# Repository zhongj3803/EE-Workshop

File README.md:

# EE-Workshop
Repository for EE Workshop material

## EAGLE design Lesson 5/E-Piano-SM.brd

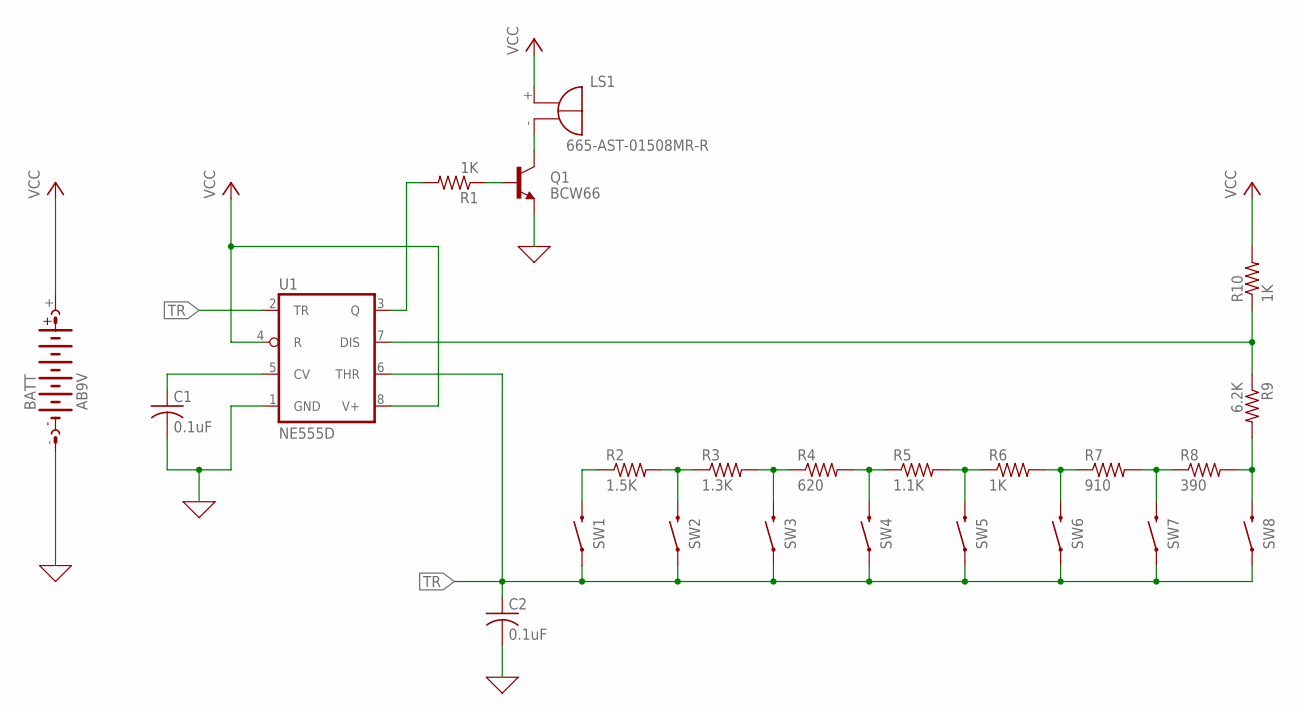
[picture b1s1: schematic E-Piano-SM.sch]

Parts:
BATT: AB9V
C1, C2: 0.1uF; C0805; MOUSER# 791-MT21B104K500CT
LS1: F/HMB; MOUSER# 665-AST-01508MR-R
Q1: BCW66; SOT23-BEC; MOUSER# 726-BCW66KHE6327HTSA
R1, R6, R10: 1K; R0805; MOUSER# 652-CR0805FX-1001ELF
R2: 1.5K; R0805; MOUSER# 652-CR0805FX-1501ELF
R3: 1.3K; R0805; MOUSER# 652-CR0805JW-132ELF
R4: 620; R0805; MOUSER# 652-CR0805JW-621ELF
R5: 1.1K; R0805; MOUSER# 652-CR0805FX-1101ELF
R7: 910; R0805; MOUSER# 652-CR0805FX-9100ELF
R8: 390; R0805; MOUSER# 652-CR0805JW-391ELF
R9: 6.2K; R0805; MOUSER# 652-CR0805FX-6201ELF
SW1, SW2, SW3, SW4, SW5, SW6, SW7, SW8: MOMENTARY-SWITCH-SPST-SMD-6.2MM-TALL; TACTILE_SWITCH_SMD_6.2MM_TALL; MOUSER# 653-B3F-1000
U1: NE555D; SO08; MOUSER# 595-TLC555CDR

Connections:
0: BATT.-, C1.2, C2.2, Q1.E, U1.1 (GND)
unnamed: R8.2, R9.2, SW8.B2 (2)
unnamed: R9.1, R10.1, U1.7 (DIS)
unnamed: R2.1, SW1.B2 (2)
unnamed: R7.2, R8.1, SW7.B2 (2)
unnamed: R6.2, R7.1, SW6.B2 (2)
unnamed: R5.2, R6.1, SW5.B2 (2)
unnamed: R4.2, R5.1, SW4.B2 (2)
unnamed: R3.2, R4.1, SW3.B2 (2)
unnamed: R2.2, R3.1, SW2.B2 (2)
unnamed: R1.2, U1.3 (Q)
unnamed: C1.1, U1.5 (CV)
unnamed: LS1.-, Q1.C
unnamed: Q1.B, R1.1
TR: C2.1, SW1.A2 (1), SW2.A2 (1), SW3.A2 (1), SW4.A2 (1), SW5.A2 (1), SW6.A2 (1), SW7.A2 (1), SW8.A2 (1), U1.2 (TR), U1.6 (THR)
VCC: BATT.+, LS1.+, R10.2, U1.4 (R), U1.8 (V+)

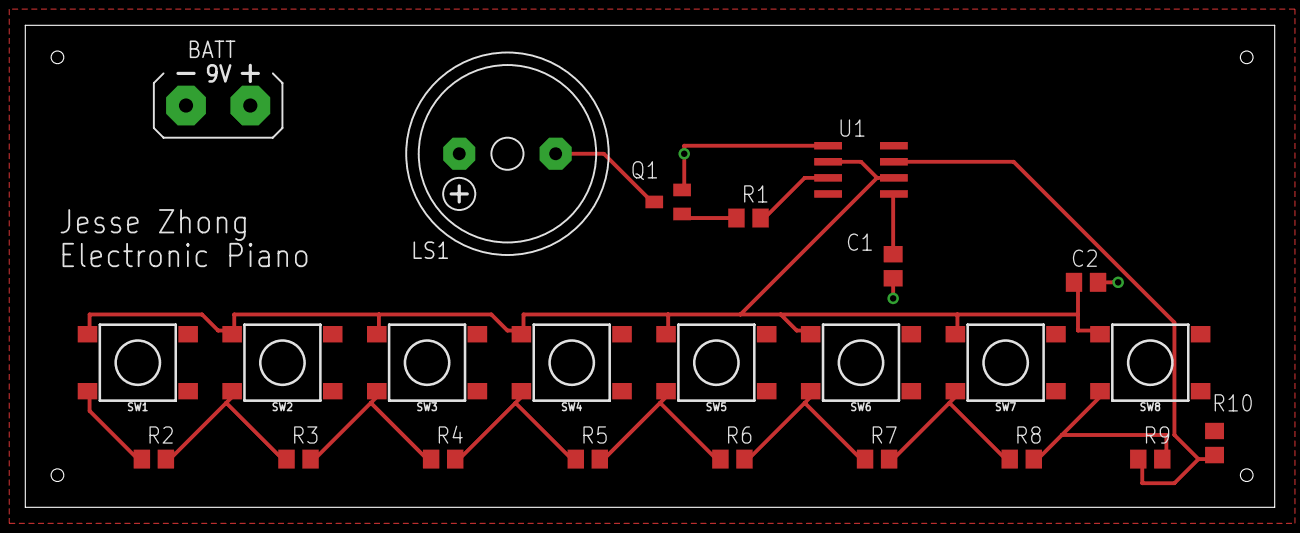
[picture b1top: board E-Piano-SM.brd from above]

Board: 2 copper layers, 98.7 x 38.1 mm, 24 parts (0 on the bottom side), 16 nets.

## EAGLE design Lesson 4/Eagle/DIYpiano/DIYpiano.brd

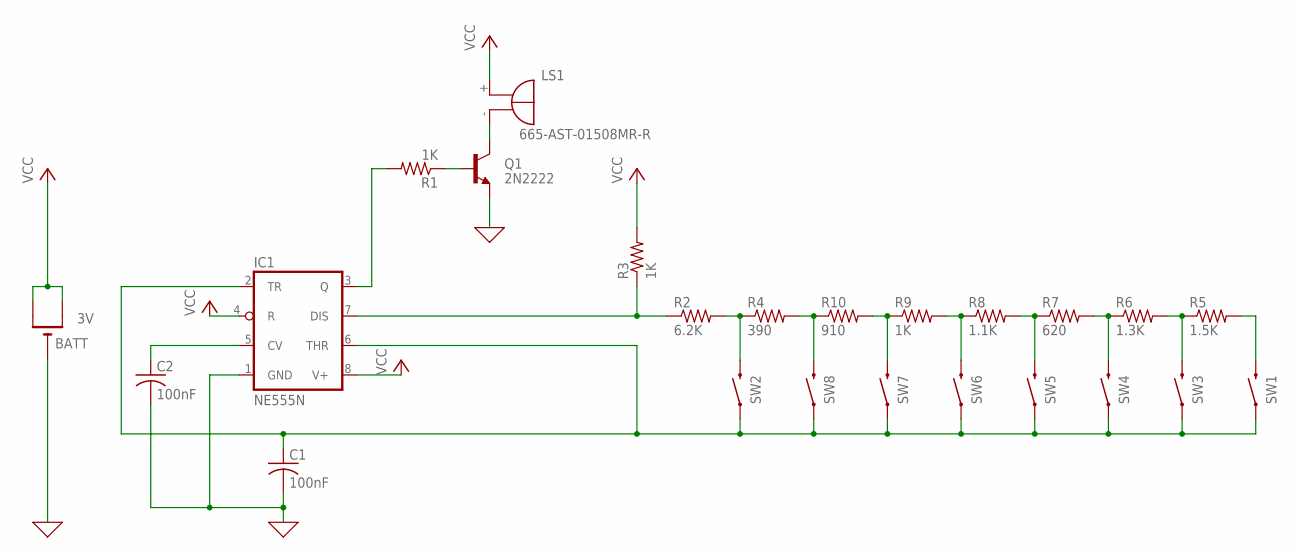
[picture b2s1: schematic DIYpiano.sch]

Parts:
BATT: 3V; CR1220-THM; MOUSER# 534-3001
C1, C2: 100nF; C025-025X050; MOUSER# 581-SR201C104KARTR1
IC1: NE555N; DIL08; MOUSER# 595-TLC555CP
LS1: F/HMB; MOUSER# 665-AST-01508MR-R
Q1: 2N2222; TO92-E1; MOUSER# 833-PN2222A-AP
R1, R3, R9: 1K; 0207/10; MOUSER# 660-MF1/4DCT26A1001F
R2: 6.2K; 0207/10; MOUSER# 603-MFR-25FRF52-6K2
R4: 390; 0207/10; MOUSER# 603-MFR-25FTE52-390R
R5: 1.5K; 0207/10; MOUSER# 603-MFR-25FBF52-1K5
R6: 1.3K; 0207/10; MOUSER# 603-MFR-25FBF52-1K3
R7: 620; 0207/10; MOUSER# 603-MFR-25FBF52-620R
R8: 1.1K; 0207/10; MOUSER# 603-MFR-25FBF52-1K1
R10: 910; 0207/10; MOUSER# 603-MFR-25FRF52-910R
SW1, SW2, SW3, SW4, SW5, SW6, SW7, SW8: MOMENTARY-SWITCH-SPST-PTH-6.0MM; TACTILE_SWITCH_PTH_6.0MM; MOUSER# 653-B3F-1000

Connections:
GND: BATT.-, C1.2, C2.2, IC1.1 (GND), Q1.3 (E)
unnamed: R2.2, R4.1, SW2.3 (2)
unnamed: IC1.7 (DIS), R2.1, R3.1
unnamed: C1.1, IC1.2 (TR), IC1.6 (THR), SW1.1, SW2.1, SW3.1, SW4.1, SW5.1, SW6.1, SW7.1, SW8.1
unnamed: R4.2, R10.1, SW8.3 (2)
unnamed: R9.1, R10.2, SW7.3 (2)
unnamed: R8.1, R9.2, SW6.3 (2)
unnamed: R7.1, R8.2, SW5.3 (2)
unnamed: R6.1, R7.2, SW4.3 (2)
unnamed: R5.1, R6.2, SW3.3 (2)
unnamed: R5.2, SW1.3 (2)
unnamed: IC1.3 (Q), R1.2
unnamed: C2.1, IC1.5 (CV)
unnamed: LS1.-, Q1.1 (C)
unnamed: Q1.2 (B), R1.1
VCC: BATT.+1 (+), BATT.+2 (+1), IC1.4 (R), IC1.8 (V+), LS1.+, R3.2

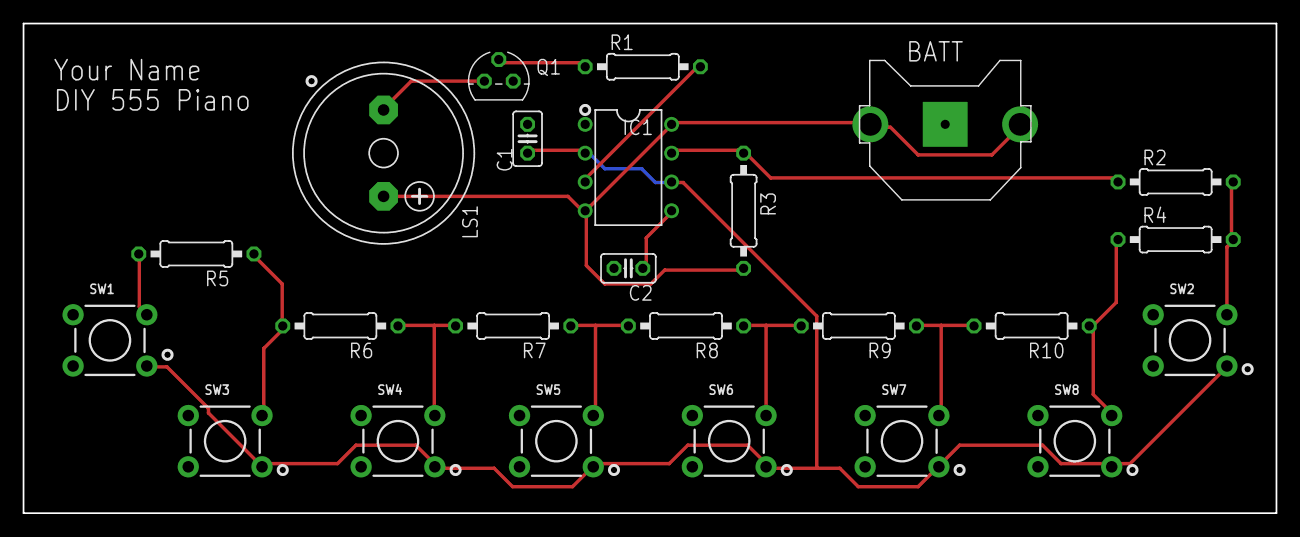
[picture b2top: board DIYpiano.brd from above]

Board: 2 copper layers, 110.5 x 43.2 mm, 24 parts (0 on the bottom side), 16 nets.

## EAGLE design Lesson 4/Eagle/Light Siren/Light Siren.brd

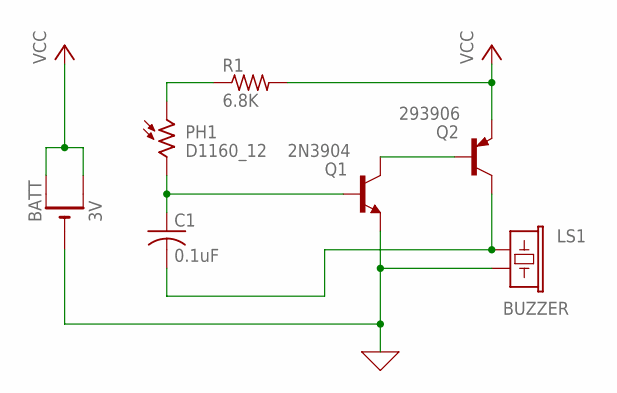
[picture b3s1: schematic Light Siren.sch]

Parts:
BATT: 3V; CR1220-THM
C1: 0.1uF; C025-025X050
LS1: BUZZER; BUZZER-12MM-NS
PH1: D1160_12; D11XX
Q1: 2N3904; TO92
Q2: 293906; TO92
R1: 6.8K; 0207/10

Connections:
0: BATT.-, LS1.- (2), Q1.1 (E)
unnamed: PH1.1, R1.1
unnamed: C1.2, LS1.+ (1), Q2.3 (C)
unnamed: Q1.3 (C), Q2.2 (B)
unnamed: C1.1, PH1.2, Q1.2 (B)
VCC: BATT.+1 (+), BATT.+2 (+1), Q2.1 (E), R1.2

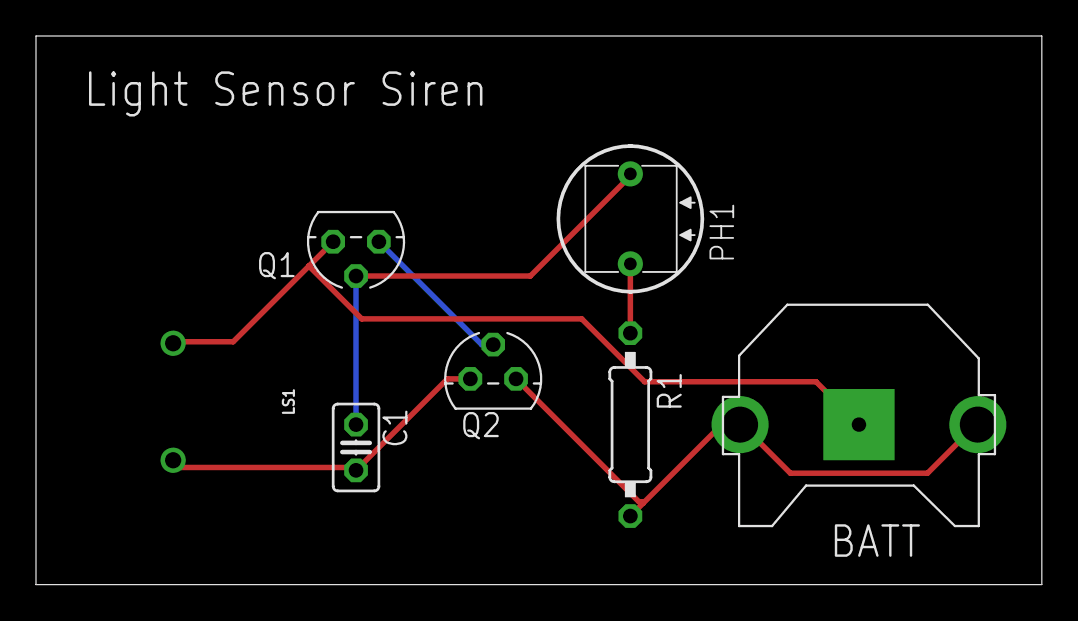
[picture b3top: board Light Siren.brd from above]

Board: 2 copper layers, 55.9 x 30.5 mm, 7 parts (0 on the bottom side), 6 nets.

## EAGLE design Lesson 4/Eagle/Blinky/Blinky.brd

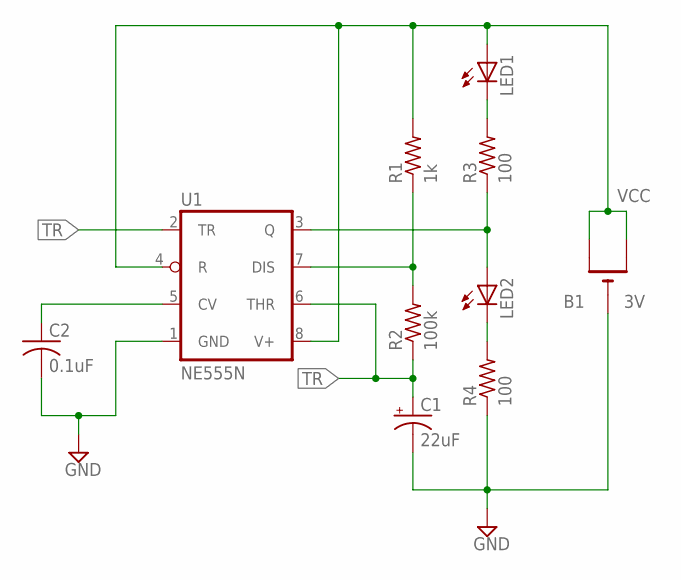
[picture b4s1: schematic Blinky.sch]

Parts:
B1: 3V; CR1220-THM
C1: 22uF; E1,8-4
C2: 0.1uF; C025-025X050
LED1, LED2: LED5MM
R1: 1k; 0309/12
R2: 100k; 0309/12
R3, R4: 100; 0309/12
U1: NE555N; DIL08

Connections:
GND: B1.-, C1.-, C2.2, R4.1, U1.1 (GND)
unnamed: C2.1, U1.5 (CV)
unnamed: R1.1, R2.2, U1.7 (DIS)
unnamed: LED2.A, R3.1, U1.3 (Q)
unnamed: LED2.K (C), R4.2
unnamed: LED1.K (C), R3.2
TR: C1.+, R2.1, U1.2 (TR), U1.6 (THR)
VCC: B1.+1 (+), B1.+2 (+1), LED1.A, R1.2, U1.4 (R), U1.8 (V+)

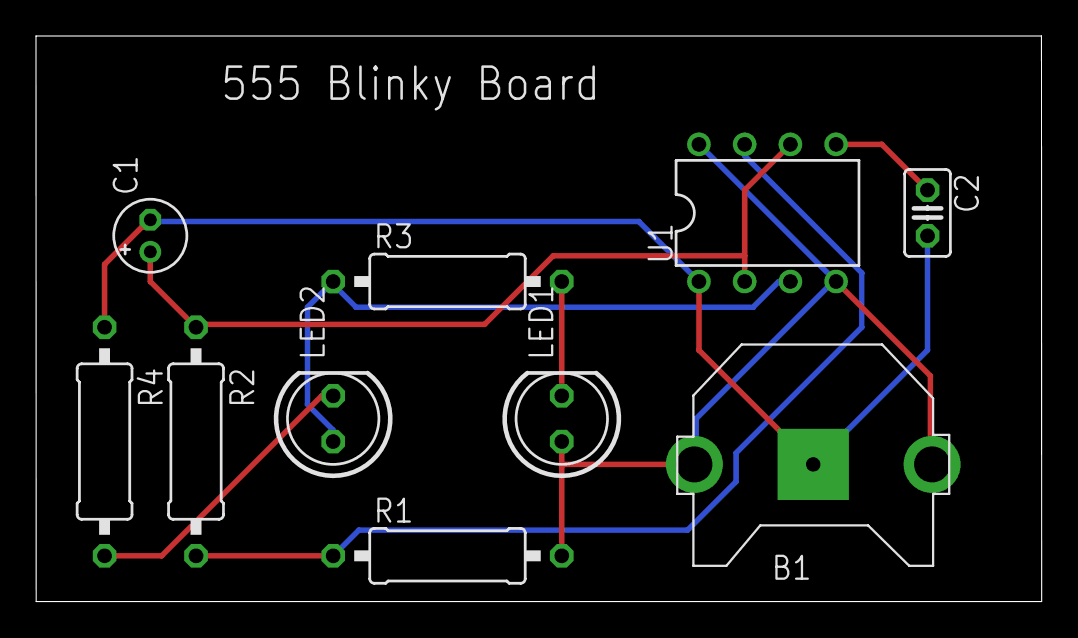
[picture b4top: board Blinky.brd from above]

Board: 2 copper layers, 55.9 x 31.4 mm, 10 parts (0 on the bottom side), 8 nets.

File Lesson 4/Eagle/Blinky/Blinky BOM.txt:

Partlist exported from C:/Users/Parents/Documents/League/GitHub/EE-Workshop/Lesson 4/Eagle/Blinky/Blinky.sch at 12/1/2018 8:56 AM

Part Value  Device          Package      Description                                    SPICEPREFIX
B1   3V     CR1220THM       CR1220-THM   CR1216/CR1220/CR1225 12mm 3V lithium coin cell J          
C1   22uF   CPOL-USE1.8-4   E1,8-4       POLARIZED CAPACITOR, American symbol           C          
C2   0.1uF  C-US025-025X050 C025-025X050 CAPACITOR, American symbol                     C          
LED1        LED5MM          LED5MM       LED                                                       
LED2        LED5MM          LED5MM       LED                                                       
R1   1k     R-US_0309/12    0309/12      RESISTOR, American symbol                      R          
R2   100k   R-US_0309/12    0309/12      RESISTOR, American symbol                      R          
R3   100    R-US_0309/12    0309/12      RESISTOR, American symbol                      R          
R4   100    R-US_0309/12    0309/12      RESISTOR, American symbol                      R          
U1   NE555N NE555N          DIL08        TIMER                                          X

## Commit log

2018-10-19 Initial upload of LTSpice schematics
2018-10-19 Updating the Circuits directory
    Many new schematics and accomponying spreadsheets have been added.
    Pendant was moved from LTSpice to the "Circuits" directory.
2018-11-09 Updates and upload of the Pentdant Design
2018-11-16 Loaded material for lesson 2
2018-11-16 Initial upload of the project for Workshop Lesson 3.
2018-11-17 Latest updatea to lesson 3's project
2018-11-17 Completed Lesson 3's Project
2018-11-17 Updates to the Workshop directory
    Moved individual circuits to their own directories.
    Updated Lesson 3's project.
2018-11-28 Updated legal terms
2018-11-30 Upload of Lesson 4
2018-12-01 Updates to the Lesson 4 Circuits
    Updated schematics and board layout for Blinky and DIYPiano.
    Created schematics for Light Siren.
2018-12-05 Updated legal language for all lesson material
2018-12-07 Updates to lesson 4 and its circuits
2018-12-08 Updates to the Blinky circuits
2018-12-14 Created BOM and PL for DIY Piano
2018-12-15 Updates to the BOM/PL of DIY Piano circuit
2018-12-15 Upload of Eagle layout tutorial
2018-12-15 Added Board Fabrication Tutorial
2019-01-11 Clean up of repo
2019-04-24 Added DIY Battery slides to Workshop Lesson 1
2019-04-24 Upload of Lesson 5
2019-05-01 Update to Workshop Lesson 2
2019-05-07 Electronic piano Gerber file update
2019-05-07 Updates to Lesson 3 project/lab worksheet.
2019-05-14 Updated Workshop Lesson 4
    Extensive update to tutorials and schematics.
2019-05-15 Updates to Workshop Lesson 4
2019-05-21 Updates to Lesson 4 and 5
2019-06-13 Cleaning up Workshop material.
2019-06-25 Updated Lesson 2
2019-06-27 Updates to Lesson 3 and 4
2019-06-27 Updates to Lesson 4
2019-06-28 Updated Lessons 4 and 5
2019-06-29 Updated Lesson 5
2019-08-15 Finished Schematic
2019-08-16 FInished Board

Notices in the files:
parts and their libraries:
SparkFun-Switches: Licensing: Creative Commons ShareAlike 4.0 International - https://creativecommons.org/licenses/by-sa/4.0
